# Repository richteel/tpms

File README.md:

# Raspberry Pi Pico Tire/Tyre Pressure Monitoring System (TPMS) Monitor

The Tire light was illuminated on the dash of my 2007 Prius. I ran around checking the air pressure in the tires. Found that a few were perhaps a little low, but not enough to cause the dash light to be lit. I then assumed that one or more of the TPMS sensors had a dead battery, but how can I know for certain? I took it to the garage and found that yes, one was dead and one had a low battery. The garage replaced them both. This got me to look and see if anyone had built a TPMS display to show the pressure and temperature of each tire.

After searching a bit, I came across an article on <a href="https://www.hackster.io/jsmsolns/arduino-tpms-tyre-pressure-display-b6e544" target="_blank">hackster.io</a> titled, "Arduino TPMS Tyre Pressure Display". It was just the thing I was looking for. I wanted to use a Raspberry Pi Pico as I have a few of them here, but the code posted does not support the RP2040 micro-controller used in the Raspberry Pi Pico. I was able to modify the code to work with the RP2040. My code will be available on GitHub at <a href="https://github.com/richteel/tpms" target="_blank">https://github.com/richteel/tpms</a> and some posts available at <a href="https://teelsys.com/" target="_blank">https://teelsys.com/</a>.

Newer cars have the details of the TPMS built in so it is not necessary to guess, but my older Prius does not. With this project, I will be able to monitor the health of my tires and when on a road trip and the dash light comes on, I don't need to panic and pull over to see if it is a major issue, that needs to be resolved right away, or if it is something that I can wait until I get to my destination.

## Items used in my build ##

- <a href="https://www.adafruit.com/product/4883" target="_blank">Raspberry Pi Pico (Pimoroni Pico Lipo) NOTE: Used Earle Philhower's core</a>
- <a href="https://www.adafruit.com/product/358" target="_blank">Adafruit 1.8" Color TFT LCD display with MicroSD Card Breakout - ST7735R</a>
- <a href="https://www.amazon.com/gp/product/B0C8RRG88V/ref=ppx_yo_dt_b_asin_title_o04_s00?ie=UTF8&psc=1" target="_blank">CC1101 Radio Frequency Transceiver Module</a>
- <a href="https://www.adafruit.com/product/160" target="_blank">Buzzer</a>
- 1 10 Ohm Resistor
- 2 150 Ohm Resistors
- <a href="https://www.pcbway.com/project/shareproject/Raspberry_Pi_Pico_Tire_Tyre_Pressure_Monitoring_System_TPMS_48b6424e.html" target="_blank">PCB from PCBWay</a>

## Code Notes ##

### TPMS_Monitor ###
The code in the TPMS_Monitor folder is the original code modified to work with the Raspberry Pi Pico code using Earle Philhower's core. This code is hard coded for US 315 MHz and Toyota PMV-107J sensors.

### TPMS_Monitor2 ###
Currently a work in progress to allow configuration to any supported sensor configuration. This code is not ready for use. Code changes will be checked in occasionally as code is updated. An Excel workbook, TPMS_Monitor2.xlsx, has been added with some analysis to help with the development of the modified version.

<hr />

I hope you enjoy this project and have success building it.

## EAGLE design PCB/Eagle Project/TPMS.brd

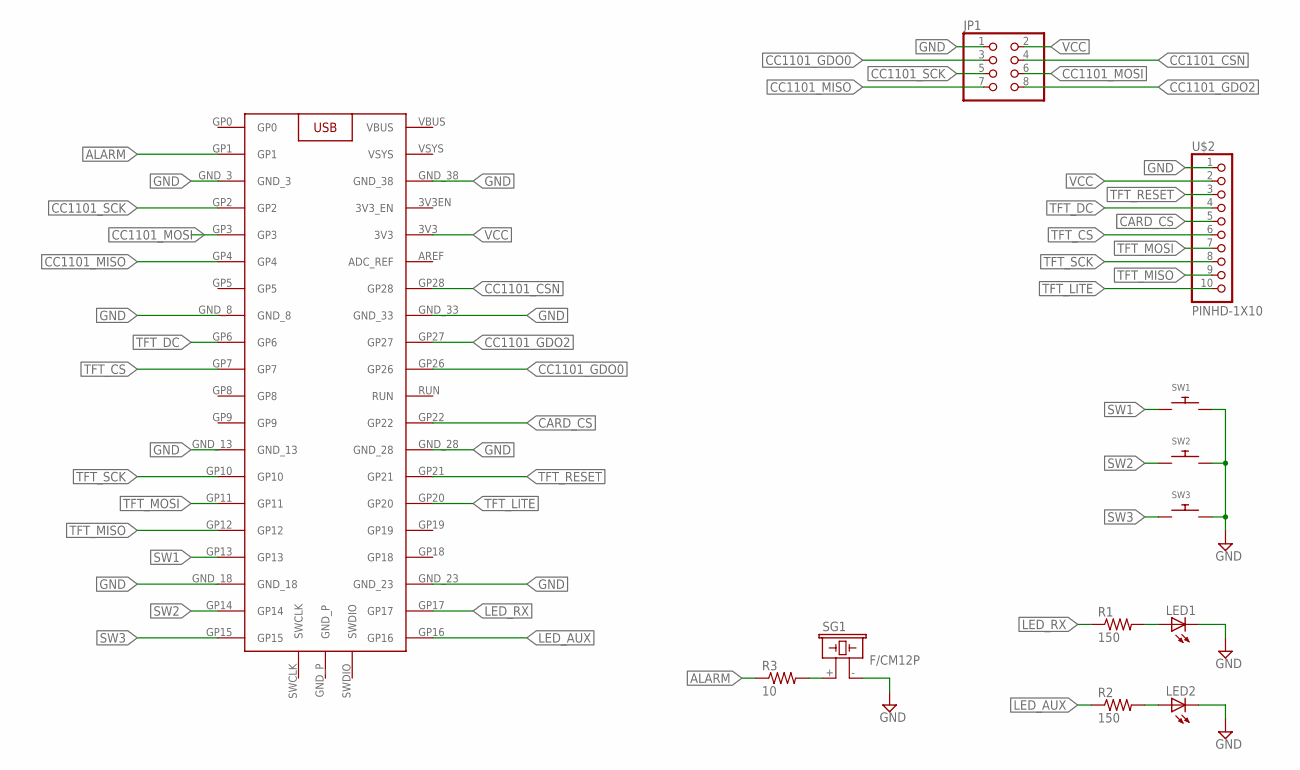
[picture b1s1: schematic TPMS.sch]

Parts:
JP1: PINHD-2X4; 2X04
LED1, LED2: LED3MM
R1, R2: 150; M0805
R3: 10; M0805
SG1: F/CM12P
SW1, SW2, SW3: SWITCH_PUSHBUTTONEVQ-PE; TACT_PANA-EVQ
U$1: RASPBERRY_PI_PICORASPBERRY_PI_PICO; RASPBERRY_PI_PICO
U$2: PINHD-1X10; 1X10-BIG

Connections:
ALARM: R3.1, U$1.GP1
CARD_CS: U$1.GP22, U$2.5
CC1101_CSN: JP1.4, U$1.GP28
CC1101_GDO0: JP1.3, U$1.GP26
CC1101_GDO2: JP1.8, U$1.GP27
CC1101_MISO: JP1.7, U$1.GP4
CC1101_MOSI: JP1.6, U$1.GP3
CC1101_SCK: JP1.5, U$1.GP2
GND: JP1.1, LED1.K (C), LED2.K (C), SG1.- (2), SW1.P$2, SW2.P$2, SW3.P$2, U$1.GND_3, U$1.GND_8, U$1.GND_13, U$1.GND_18, U$1.GND_23, U$1.GND_28, U$1.GND_33, U$1.GND_38, U$2.1
LED_AUX: R2.1, U$1.GP16
LED_RX: R1.1, U$1.GP17
unnamed: LED1.A, R1.2
unnamed: LED2.A, R2.2
unnamed: R3.2, SG1.+ (1)
SW1: SW1.P$1, U$1.GP13
SW2: SW2.P$1, U$1.GP14
SW3: SW3.P$1, U$1.GP15
TFT_CS: U$1.GP7, U$2.6
TFT_DC: U$1.GP6, U$2.4
TFT_LITE: U$1.GP20, U$2.10
TFT_MISO: U$1.GP12, U$2.9
TFT_MOSI: U$1.GP11, U$2.7
TFT_RESET: U$1.GP21, U$2.3
TFT_SCK: U$1.GP10, U$2.8
VCC: JP1.2, U$1.3V3, U$2.2

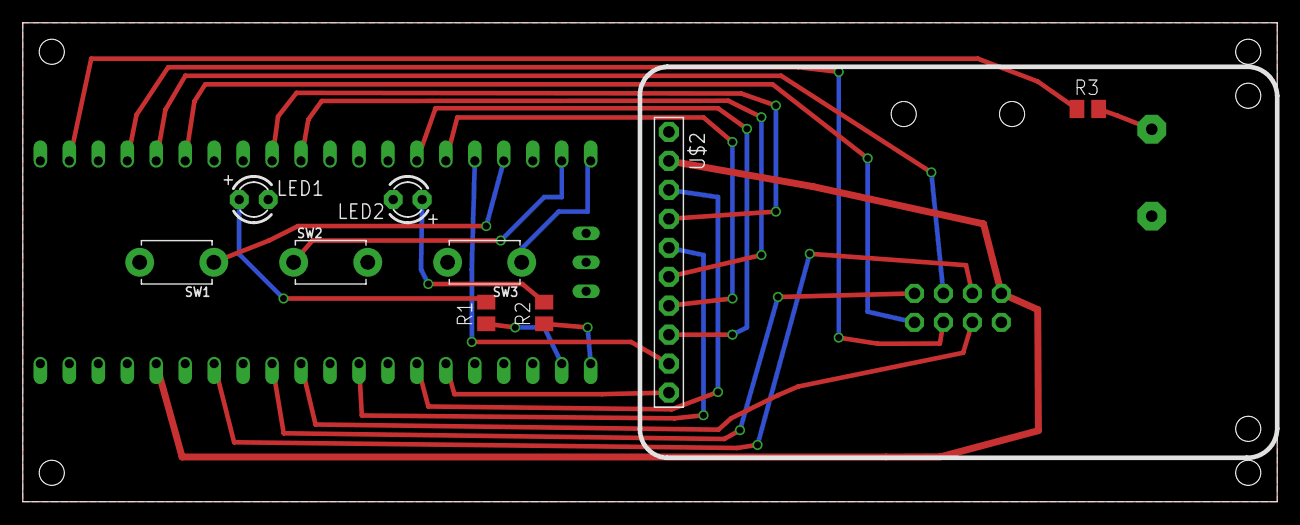
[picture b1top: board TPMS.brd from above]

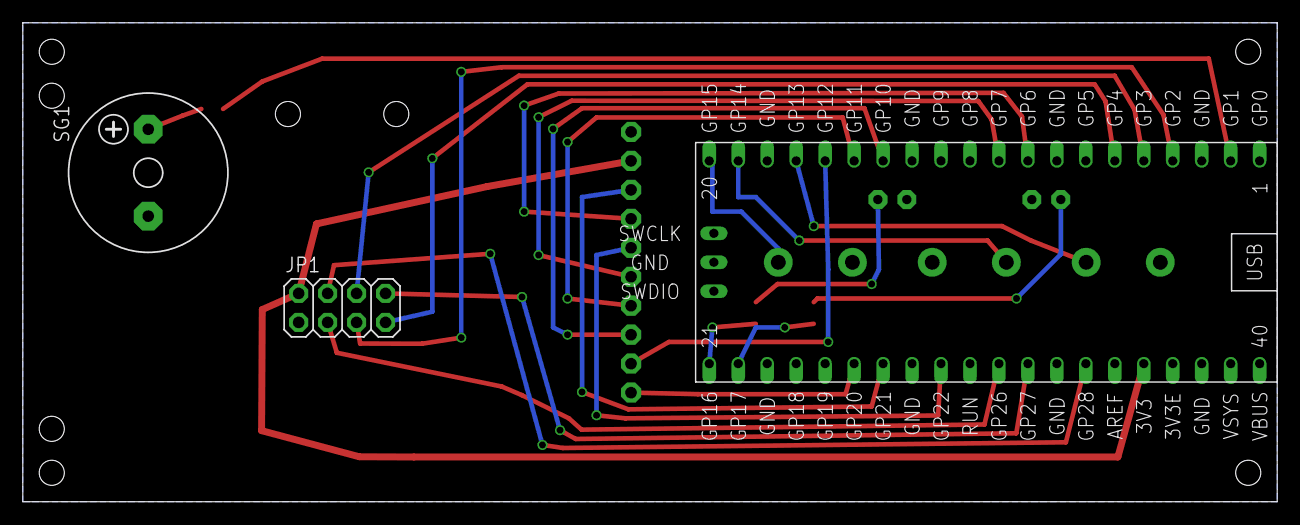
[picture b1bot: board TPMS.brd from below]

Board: 2 copper layers, 110.0 x 42.0 mm, 12 parts (3 on the bottom side), 25 nets.

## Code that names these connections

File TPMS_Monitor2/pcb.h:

#ifndef CONFIG_H
#define CONFIG_H

#define DISPLAY_1_INCH_YB_I2C_DISPLAY_ADAFRUIT 8192    // 0.96in SSD1306 I2C 64x128 OLED display Adafruit
#define DISPLAY_1_INCH_YB_I2C_DISPLAY          8193    // 0.96in SSD1306 I2C 64x128 OLED display
#define DISPLAY_2_INCH_ST7735_DISPLAY         20480    // 1.8in ST7735 SPI 160x128 TFT display
#define DISPLAY_2_INCH_ST7789_DISPLAY         57600    // 1.28in ST7789 SPI 240x240 TFT round display
#define DISPLAY_24_INCH_ILI9341_DISPLAY       76800    // 2.4in ILI9341 SPI 240x320 TFT display

/*****************************************************************************
 *                        Board and Module Parameters                        *
 *****************************************************************************/
#define PCB_VERSION_MAJ     1
#define PCB_VERSION_MIN     0
#define SER                 Serial
#define DEBUG               true
#define USE_HW_CD           true
#define USE_FIFO            false

#if PCB_VERSION_MAJ == 1
  #define PROC_TYPE         "Raspberry Pi Pico RP2040"
  #define USE_DISPLAY       DISPLAY_2_INCH_ST7735_DISPLAY

  /*************/
  /*    PINS   */
  /*************/

  /**** SPI ****/
  // CC1101
  #define CC1101_SPI        SPI
  #define CC1101_SCK        2
  #define CC1101_MOSI       3
  #define CC1101_MISO       4

  // LCD
  #define LCD_SPI           SPI1
  #define LCD_SCK           10
  #define LCD_MOSI          11
  #define LCD_MISO          12

  /**** CC1101 ****/
  #define CC1101_CD         26    //Comment line if not wired, otherwise CD pin status is received over SPI
  #define CC1101_RX         27    //must be an ext interrupt pin
  #define CC1101_CS         28    // Define the Chip Select pin

  /**** LCD/SD CARD ****/
  #define LCD_DC            6     // D/C
  #define LCD_CS            7     // LCD_CS
  #define LCD_LITE          20    // Backlight
  #define LCD_RESET         21    // Reset
  #define SDCARD_CS         22    // Card_CS

  /**** LEDS ****/
  #define LED_DEFAULT       25    // Built in LED
  #define LED_RX            17    // RX LED  - Red
  #define LED_AUX           16    // AUX LED - Yellow
  #define LED_DBUG          18    // Debug LED - Green

  /**** BUZZER ****/
  #define BUZZER            1

  /**** SWICHES ****/
  #define SW_BACK           13
  #define SW_SELECT         14
  #define SW_NEXT           15

  /*****************/
  /* ACTIVE LEVELS */
  /*****************/
  #define ACTIVE_BUZZER     HIGH    // Logic level to sound the buzzer
  #define ACTIVE_SW         LOW     // Logic level when button is pressed
  #define ACTIVE_LED        HIGH    // Logic level to light LED

#else
  #error No configuration set up for this PCB Version in config.h
#endif  // PCB_VERSION == 1



/*****************/
/*   MAX VALUES  */
/*****************/
#define MAXBITS             1000
#define MAXTIMINGS          900


/******************************************/
/*    End Configuration Perform Checks    */
/******************************************/
#ifndef DEBUG
  #define DEBUG             false
#endif

#ifndef USE_DISPLAY
  #define USE_DISPLAY       0
#endif

#ifndef PROC_TYPE
  #error PROC_TYPE not defined in config.h
#endif

#ifndef CC1101_SPI
  #error No configuration set up for CC1101 in config.h
#elif !defined(CC1101_RX) || !defined(CC1101_CS)
  #error CC1101 RX and CS pins not defined in config.h
#endif

#if defined(LCD_SPI) && (!defined(LCD_SCK) || !defined(LCD_MOSI) || !defined(LCD_MISO) || !defined(LCD_DC) || !defined(LCD_CS) || !defined(LCD_RESET) || !defined(LCD_LITE))
  #error LCD SCK, MOSI, MISO, LCD_DC, LCD_CS, LCD_RESET, and LCD_LITE pins not defined in config.h
#endif

#if (defined(LED_DEFAULT) || defined(LED_RX) || defined(LED_AUX)) && !defined(ACTIVE_LED)
  #error Must define ACTIVE_LED when LED_DEFAULT, LED_RX, or LED_AUX are defined in config.h
#endif

#if defined(BUZZER) && !defined(ACTIVE_BUZZER)
  #error Must define ACTIVE_BUZZER when BUZZER is defined in config.h
#endif

#if (defined(SW_BACK) || defined(SW_SELECT) || defined(SW_NEXT)) && !defined(ACTIVE_SW)
  #error Must define ACTIVE_SW when SW_BACK, SW_SELECT, or SW_NEXT are defined in config.h
#endif

#endif    // CONFIG_H

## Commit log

2024-05-27 Adding code from hackster.io
2024-06-14 Adding additional versions available on Hackster.io.
2024-06-14 Added PCB files and initial code working with Raspberry Pi Pico and TPMS for Toyota PMV-107J.
2024-07-04 Added case files and changed code for my odd display.
2024-07-09 Update README.md
    Spelling Error
2024-07-21 TPMS-1 Updated README.md, added TPMS_Monitor2 code, and test Jira integration.
2024-07-21 Update README.md
    Fixed header tags
2024-07-21 TPMS-1 Jira did not update with last commit
